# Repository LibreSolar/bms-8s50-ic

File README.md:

# BMS 8S50 IC

 First boards tested, some issues might still be open.

Schematic: [PDF file](https://github.com/LibreSolar/bms-8s50-ic/raw/master/build/bms-8s50-ic_schematic.pdf)

Bill of Materials: [CSV file](build/bms-8s50-ic_bom.csv) or [interactive HTML BOM](https://libre.solar/bms-8s50-ic/build/bms-8s50-ic_ibom.html)

Firmware repository: [LibreSolar/bms-firmware](https://github.com/LibreSolar/bms-firmware)

## Features:

- 3 to 8 Li-ion cells (e.g. LiFePO4)
- Integrated high-side MOSFET switch and current sensor
- Balancing current approx. 150 mA
- STM32L452 ARM Cortex-M4 microcontroller
- Built-in CAN communication interface and UEXT extension connector

## Firmware

The firmware is developed in a separate repository [LibreSolar/bms-firmware](https://github.com/LibreSolar/bms-firmware).

## Housing

The PCB is designed such that a heat sink can be easily attached at the bottom. The following images show a draft idea for the housing. The files of the heat sink and the cover can be found in the `housing` folder as native FreeCAD files.

## Important Notice

The PCBs have not been tested regarding EMC and other regulations. If you reproduce the boards, you use them at your own risk and responsibility.

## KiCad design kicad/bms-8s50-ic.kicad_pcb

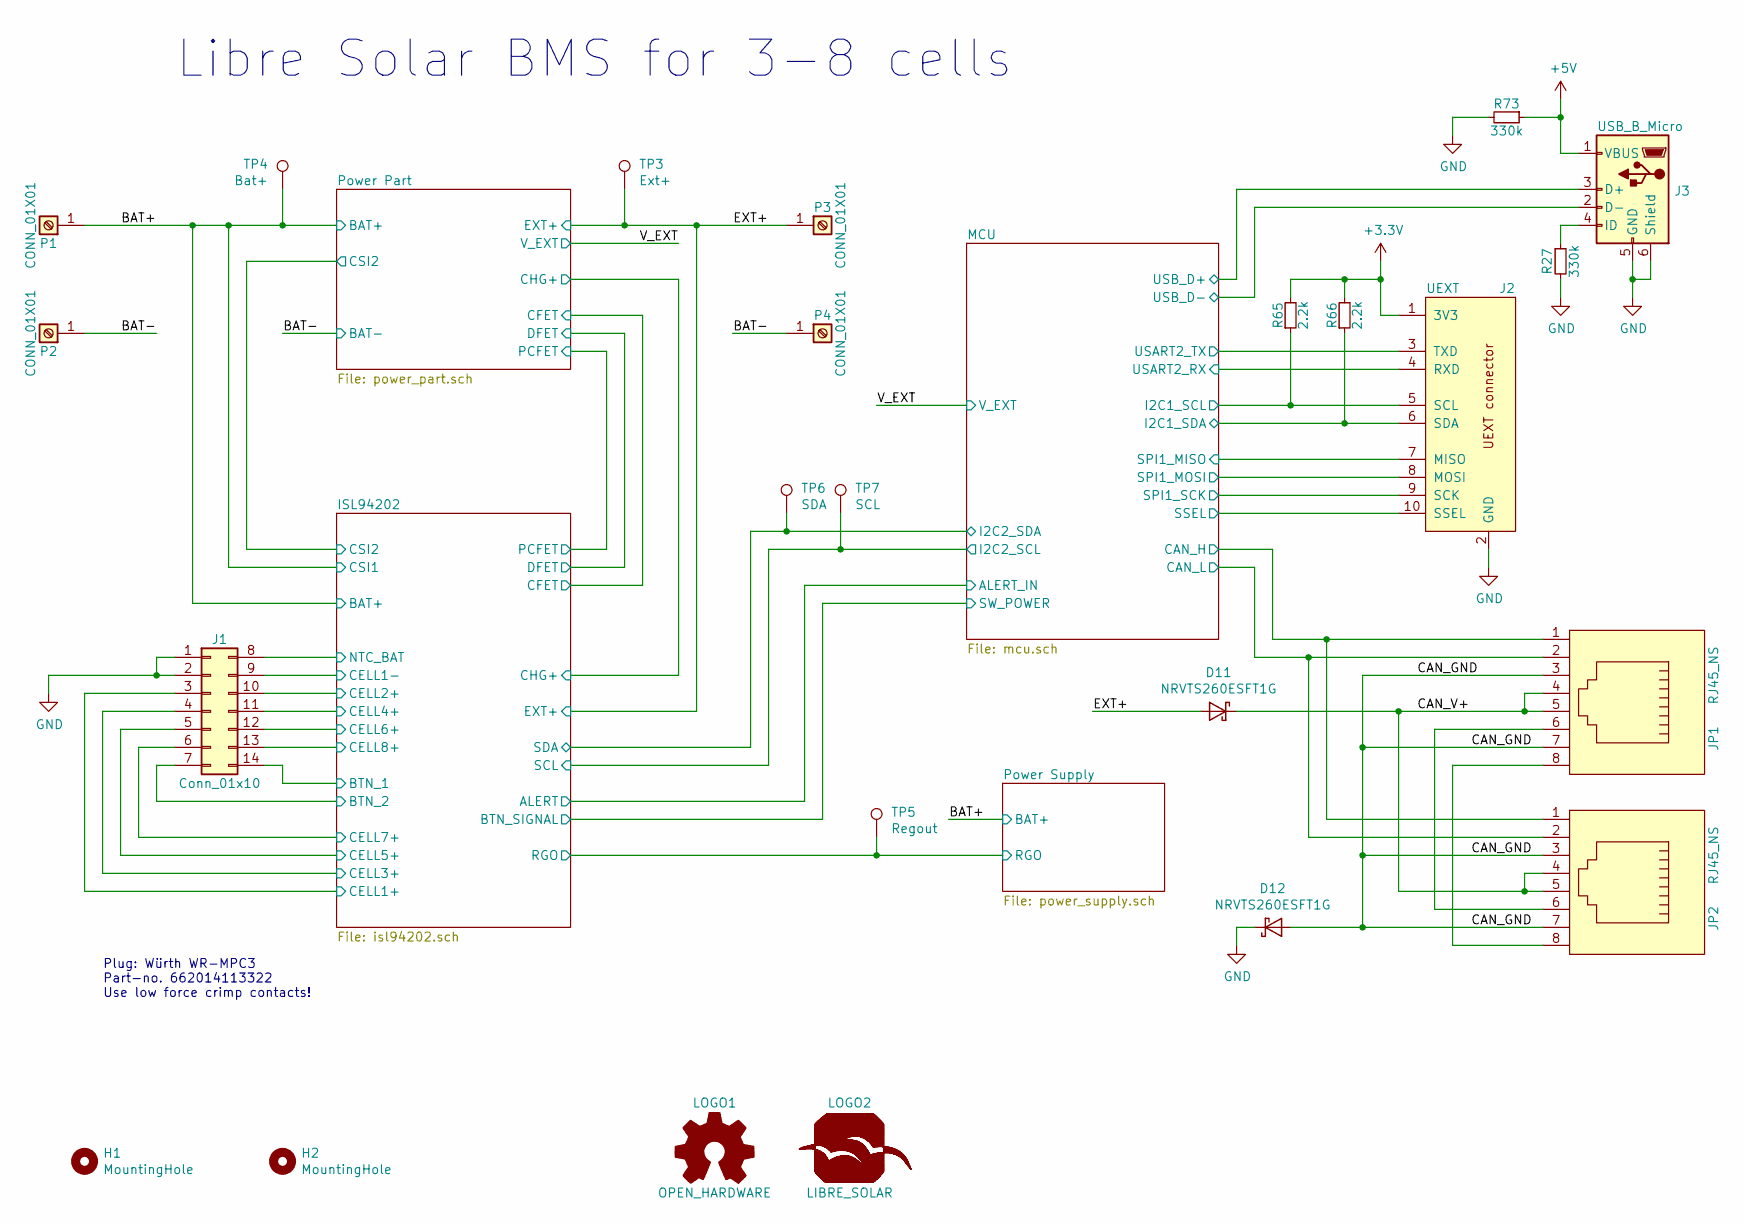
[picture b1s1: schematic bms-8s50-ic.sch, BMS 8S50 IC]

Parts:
D11, D12: NRVTS260ESFT1G; D_SOD-123; PartNumber NRVTS260ESFT1G
H1, H2: MountingHole; MountingHole_3.2mm_M3_Pad
J1: Conn_01x10; Molex_Micro-Fit_3.0_43045-1400_2x07_P3.00mm_Horizontal; PartNumber 66201421022
J2: UEXT; Box_Header_2x05x2.54mm_Straight; PartNumber 61201021621
J3: USB_B_Micro; USB_Micro-B_10103594-0001LF; PartNumber 10103594-0001LF
JP1, JP2: RJ45_NS; RJ45_8P8C; PartNumber 54602-908LF
LOGO1: OPEN_HARDWARE; OSHW-Logo_5.7x6mm_SilkScreen
LOGO2: LIBRE_SOLAR; LIBRESOLAR_LOGO
P1, P2, P4: CONN_01X01; Wuerth_WP-THRBU_74650195; PartNumber 74650195
P3: CONN_01X01; Wuerth_WP-THRBU_74650195
R27, R73: 330k; R_0603_1608; PartNumber RC0603FR-07330KL
R65, R66: 2.2k; R_0603_1608; PartNumber RC0603FR-072K2L
TP3: Ext+; TestPoint_1mm_pad
TP4: Bat+; TestPoint_1mm_pad
TP5: Regout; TestPoint_1mm_pad
TP6: SDA; TestPoint_1mm_pad
TP7: SCL; TestPoint_1mm_pad

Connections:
+3V3: J2.1 (3V3), R65.2, R66.2; also elsewhere on the board
+5V: J3.1 (VBUS), R73.1; also elsewhere on the board
/BAT+: P1.1, TP4.1; also elsewhere on the board
/BAT-: P2.1, P4.1; also elsewhere on the board
/CAN_GND: D12.2 (A), JP1.3, JP1.7, JP2.3, JP2.7
/CAN_V+: D11.1 (K), JP1.4, JP1.5, JP2.4, JP2.5
/EXT+: D11.2 (A), P3.1, TP3.1; also elsewhere on the board
/ISL94202/BTN_1: J1.14; also elsewhere on the board
/ISL94202/BTN_2: J1.7; also elsewhere on the board
/ISL94202/CELL1+: J1.3; also elsewhere on the board
/ISL94202/CELL1-: J1.9; also elsewhere on the board
/ISL94202/CELL2+: J1.10; also elsewhere on the board
/ISL94202/CELL3+: J1.4; also elsewhere on the board
/ISL94202/CELL4+: J1.11; also elsewhere on the board
/ISL94202/CELL5+: J1.5; also elsewhere on the board
/ISL94202/CELL6+: J1.12; also elsewhere on the board
/ISL94202/CELL7+: J1.6; also elsewhere on the board
/ISL94202/CELL8+: J1.13; also elsewhere on the board
/ISL94202/NTC_BAT: J1.8; also elsewhere on the board
/ISL94202/RGO: TP5.1; also elsewhere on the board
/MCU/CAN_H: JP1.1, JP2.1; also elsewhere on the board
/MCU/CAN_L: JP1.2, JP2.2; also elsewhere on the board
/MCU/I2C1_SCL: J2.5 (SCL), R65.1; also elsewhere on the board
/MCU/I2C1_SDA: J2.6 (SDA), R66.1; also elsewhere on the board
/MCU/I2C2_SCL: TP7.1; also elsewhere on the board
/MCU/I2C2_SDA: TP6.1; also elsewhere on the board
/MCU/SPI1_MISO: J2.7 (MISO); also elsewhere on the board
/MCU/SPI1_MOSI: J2.8 (MOSI); also elsewhere on the board
/MCU/SPI1_SCK: J2.9 (SCK); also elsewhere on the board
/MCU/SSEL: J2.10 (SSEL); also elsewhere on the board
/MCU/USART2_RX: J2.4 (RXD); also elsewhere on the board
/MCU/USART2_TX: J2.3 (TXD); also elsewhere on the board
/MCU/USB_D+: J3.3 (D+); also elsewhere on the board
/MCU/USB_D-: J3.2 (D-); also elsewhere on the board
GND: D12.1 (K), J1.1, J1.2, J2.2 (GND), J3.5 (GND), J3.6 (Shield), R27.2, R73.2; also elsewhere on the board
unnamed: J3.4 (ID), R27.1
unnamed: JP1.6, JP2.6
unnamed: JP1.8, JP2.8

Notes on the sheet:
Plug: Würth WR-MPC3 Part-no. 662014113322 Use low force crimp contacts!
Libre Solar BMS for 3-8 cells

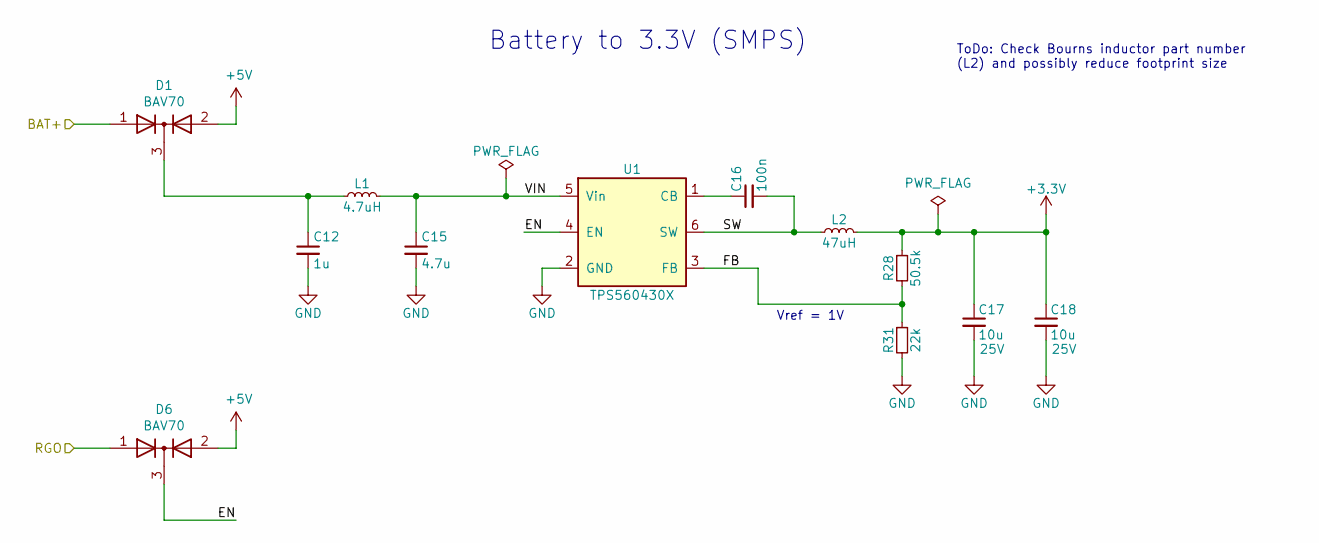
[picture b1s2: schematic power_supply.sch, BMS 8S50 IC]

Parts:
C12: 1u; C_0603_1608; PartNumber GRT188R61H105KE13D
C15: 4.7u; C_1210_3225; PartNumber GRM31CR71H475MA12L
C16: 100n; C_0603_1608; PartNumber CC0603KRX7R9BB104
C17, C18: 10u; C_0805_2012; PartNumber GRM21BR61E106KA73L
D1, D6: BAV70; SOT-23; PartNumber BAV70LT1G
L1: 4.7uH; L_0805_2012Metric; PartNumber LQM21PN4R7NGRD
L2: 47uH; Bourns_SRN6045TA; PartNumber NR6045T470M
R28: 50.5k; R_0603_1608; PartNumber RC0603FR-0750K5L
R31: 22k; R_0603_1608; PartNumber RC0603FR-0722KL
U1: TPS560430X; SOT-23-6; PartNumber TPS560430XDBVR

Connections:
+3V3: C17.1, C18.1, L2.2, R28.1; also elsewhere on the board
+5V: D1.2 (A), D6.2 (A); also elsewhere on the board
/BAT+: D1.1 (A); also elsewhere on the board
/ISL94202/RGO: D6.1 (A); also elsewhere on the board
/Power Supply/EN: D6.3 (K), U1.4 (EN)
/Power Supply/FB: R28.2, R31.1, U1.3 (FB)
/Power Supply/SW: C16.2, L2.1, U1.6 (SW)
/Power Supply/VIN: C15.1, L1.2, U1.5 (Vin)
GND: C12.2, C15.2, C17.2, C18.2, R31.2, U1.2 (GND); also elsewhere on the board
unnamed: C12.1, D1.3 (K), L1.1
unnamed: C16.1, U1.1 (CB)

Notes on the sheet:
Battery to 3.3V (SMPS)
ToDo: Check Bourns inductor part number (L2) and possibly reduce footprint size
Vref = 1V

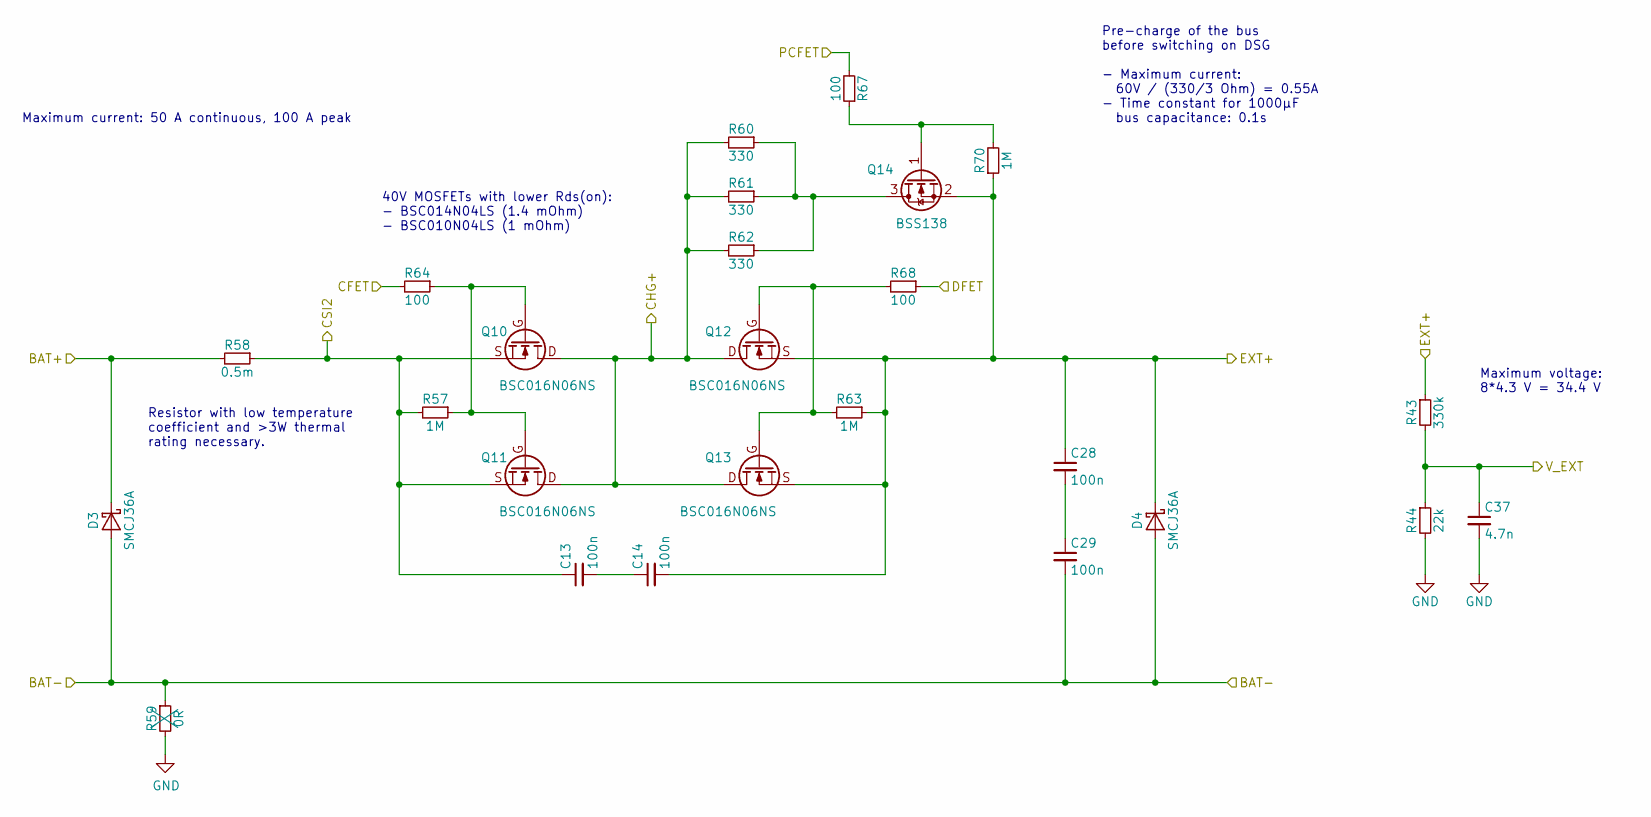
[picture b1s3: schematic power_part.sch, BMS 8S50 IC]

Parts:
C13, C14, C28, C29: 100n; C_0603_1608; PartNumber CC0603KRX7R9BB104
C37: 4.7n; C_0603_1608; PartNumber CC0603KRX7R9BB472
D3, D4: SMCJ36A; D_SMC; PartNumber SMCJ24A
Q10, Q11, Q12, Q13: BSC016N06NS; 5X6_MOSFET; PartNumber BSC016N06NS
Q14: BSS138; SOT-23; PartNumber BSS138
R43: 330k; R_0603_1608; PartNumber RC0603FR-07330KL
R44: 22k; R_0603_1608; PartNumber RC0603FR-0722KL
R57, R63, R70: 1M; R_0603_1608; PartNumber RC0603FR-071ML
R58: 0.5m; R_Shunt_2512; PartNumber WSLF2512L5000FEA
R59: 0R; R_0603_1608; PartNumber RC0603FR-070RL
R60, R61, R62: 330; R_2010_5025; PartNumber RC2010JK-07330RL
R64, R67, R68: 100; R_0603_1608; PartNumber RC0603FR-07100RL

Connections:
/BAT+: D3.1 (K), R58.2; also elsewhere on the board
/BAT-: C29.2, D3.2 (A), D4.2 (A), R59.1; also elsewhere on the board
/EXT+: C14.2, C28.1, D4.1 (K), Q12.S, Q13.S, Q14.2 (S), R43.1, R63.1, R70.1; also elsewhere on the board
/ISL94202/CFET: R64.2; also elsewhere on the board
/ISL94202/CHG+: Q10.D, Q11.D, Q12.D, Q13.D, R60.2, R61.2, R62.2; also elsewhere on the board
/ISL94202/CSI2: C13.1, Q10.S, Q11.S, R57.2, R58.1; also elsewhere on the board
/ISL94202/DFET: R68.1; also elsewhere on the board
/ISL94202/PCFET: R67.2; also elsewhere on the board
/V_EXT: C37.1, R43.2, R44.1; also elsewhere on the board
GND: C37.2, R44.2, R59.2; also elsewhere on the board
unnamed: C13.2, C14.1
unnamed: C28.2, C29.1
unnamed: Q10.G, Q11.G, R57.1, R64.1
unnamed: Q12.G, Q13.G, R63.2, R68.2
unnamed: Q14.1 (G), R67.1, R70.2
unnamed: Q14.3 (D), R60.1, R61.1, R62.1

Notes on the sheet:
Pre-charge of the bus before switching on DSG - Maximum current: 60V / (330/3 Ohm) = 0.55A - Time constant for 1000µF bus capacitance: 0.1s
Resistor with low temperature coefficient and >3W thermal rating necessary.
Maximum current: 50 A continuous, 100 A peak
40V MOSFETs with lower Rds(on): - BSC014N04LS (1.4 mOhm) - BSC010N04LS (1 mOhm)
Maximum voltage: 8*4.3 V = 34.4 V

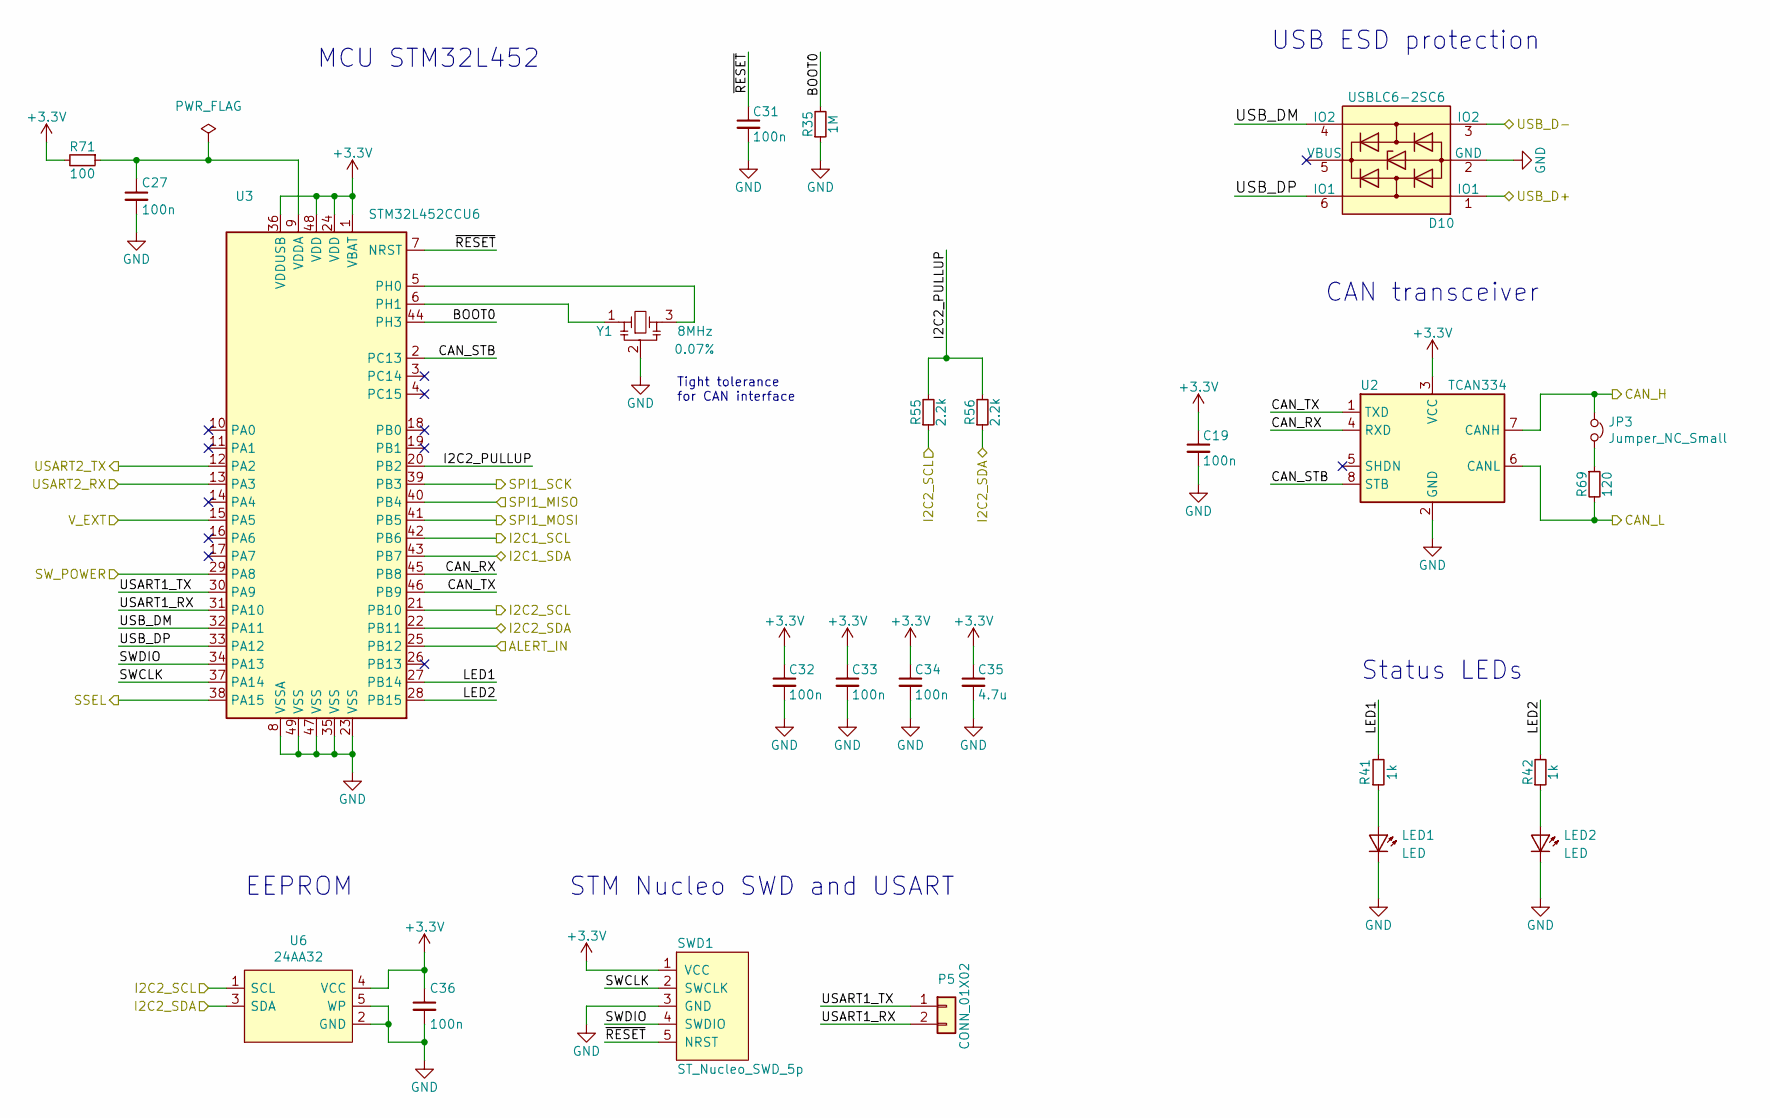
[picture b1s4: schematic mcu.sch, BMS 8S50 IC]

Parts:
C19, C27, C31, C32, C33, C34, C36: 100n; C_0603_1608; PartNumber CC0603KRX7R9BB104
C35: 4.7u; C_0603_1608; PartNumber GRM188R61A475KE15D
D10: USBLC6-2SC6; SOT-23-6; PartNumber USBLC6-2SC6
JP3: Jumper_NC_Small; PinHeader_1x02_P2.54mm_Vertical
LED1, LED2: LED; LED_0603_D3.0mm
P5: CONN_01X02; PinHeader_1x02_P2.54mm_Vertical
R35: 1M; R_0603_1608; PartNumber RC0603FR-071ML
R41, R42: 1k; R_0603_1608; PartNumber RC0603FR-071KL
R55, R56: 2.2k; R_0603_1608; PartNumber RC0603FR-072K2L
R69: 120; R_1206_3216; PartNumber RC1206FR-07120RL
R71: 100; R_0603_1608; PartNumber RC0603FR-07100RL
SWD1: ST_Nucleo_SWD_5p; PinHeader_1x05_P2.54mm_Vertical
U2: TCAN334; SOIC-8_3.9x4.9mm_Pitch1.27mm; PartNumber TCAN334DR
U3: STM32L452CCU6; QFN-48-1EP_7x7mm_P0.5mm_EP5.6x5.6mm; PartNumber STM32L452CCU6
U6: 24AA32; SOT-23-5; PartNumber 24AA32AFT-I/OT
Y1: 8MHz; Resonator_Murata_CSTNE; PartNumber CSTNE8M00GH5C000R0

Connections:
+3V3: C19.1, C32.1, C33.1, C34.1, C35.1, C36.1, R71.2, SWD1.1 (VCC), U2.3 (VCC), U3.1 (VBAT), U3.24 (VDD), U3.36 (VDDUSB), U3.48 (VDD), U6.4 (VCC); also elsewhere on the board
/ISL94202/ALERT: U3.25 (PB12); also elsewhere on the board
/ISL94202/BTN_SIGNAL: U3.29 (PA8); also elsewhere on the board
/MCU/BOOT0: R35.2, U3.44 (PH3)
/MCU/CAN_H: JP3.1, U2.7 (CANH); also elsewhere on the board
/MCU/CAN_L: R69.2, U2.6 (CANL); also elsewhere on the board
/MCU/CAN_RX: U2.4 (RXD), U3.45 (PB8)
/MCU/CAN_STB: U2.8 (STB), U3.2 (PC13)
/MCU/CAN_TX: U2.1 (TXD), U3.46 (PB9)
/MCU/I2C1_SCL: U3.42 (PB6); also elsewhere on the board
/MCU/I2C1_SDA: U3.43 (PB7); also elsewhere on the board
/MCU/I2C2_PULLUP: R55.2, R56.2, U3.20 (PB2)
/MCU/I2C2_SCL: R55.1, U3.21 (PB10), U6.1 (SCL); also elsewhere on the board
/MCU/I2C2_SDA: R56.1, U3.22 (PB11), U6.3 (SDA); also elsewhere on the board
/MCU/LED1: R41.2, U3.27 (PB14)
/MCU/LED2: R42.2, U3.28 (PB15)
/MCU/SPI1_MISO: U3.40 (PB4); also elsewhere on the board
/MCU/SPI1_MOSI: U3.41 (PB5); also elsewhere on the board
/MCU/SPI1_SCK: U3.39 (PB3); also elsewhere on the board
/MCU/SSEL: U3.38 (PA15); also elsewhere on the board
/MCU/SWCLK: SWD1.2 (SWCLK), U3.37 (PA14)
/MCU/SWDIO: SWD1.4 (SWDIO), U3.34 (PA13)
/MCU/USART1_RX: P5.2, U3.31 (PA10)
/MCU/USART1_TX: P5.1, U3.30 (PA9)
/MCU/USART2_RX: U3.13 (PA3); also elsewhere on the board
/MCU/USART2_TX: U3.12 (PA2); also elsewhere on the board
/MCU/USB_D+: D10.1 (IO1); also elsewhere on the board
/MCU/USB_D-: D10.3 (IO2); also elsewhere on the board
/MCU/USB_DM: D10.4 (IO2), U3.32 (PA11)
/MCU/USB_DP: D10.6 (IO1), U3.33 (PA12)
/MCU/~RESET: C31.1, SWD1.5 (NRST), U3.7 (NRST)
/V_EXT: U3.15 (PA5); also elsewhere on the board
GND: C19.2, C27.2, C31.2, C32.2, C33.2, C34.2, C35.2, C36.2, D10.2 (GND), LED1.1 (K), LED2.1 (K), R35.1, SWD1.3 (GND), U2.2 (GND), U3.8 (VSSA), U3.23 (VSS), U3.35 (VSS), U3.47 (VSS), U3.49 (VSS), U6.2 (GND), U6.5 (WP), Y1.2; also elsewhere on the board
unnamed: C27.1, R71.1, U3.9 (VDDA)
unnamed: JP3.2, R69.1
unnamed: LED1.2 (A), R41.1
unnamed: LED2.2 (A), R42.1
unnamed: U3.5 (PH0), Y1.3
unnamed: U3.6 (PH1), Y1.1

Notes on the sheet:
Status LEDs
MCU STM32L452
STM Nucleo SWD and USART
EEPROM
USB ESD protection
CAN transceiver
Tight tolerance for CAN interface

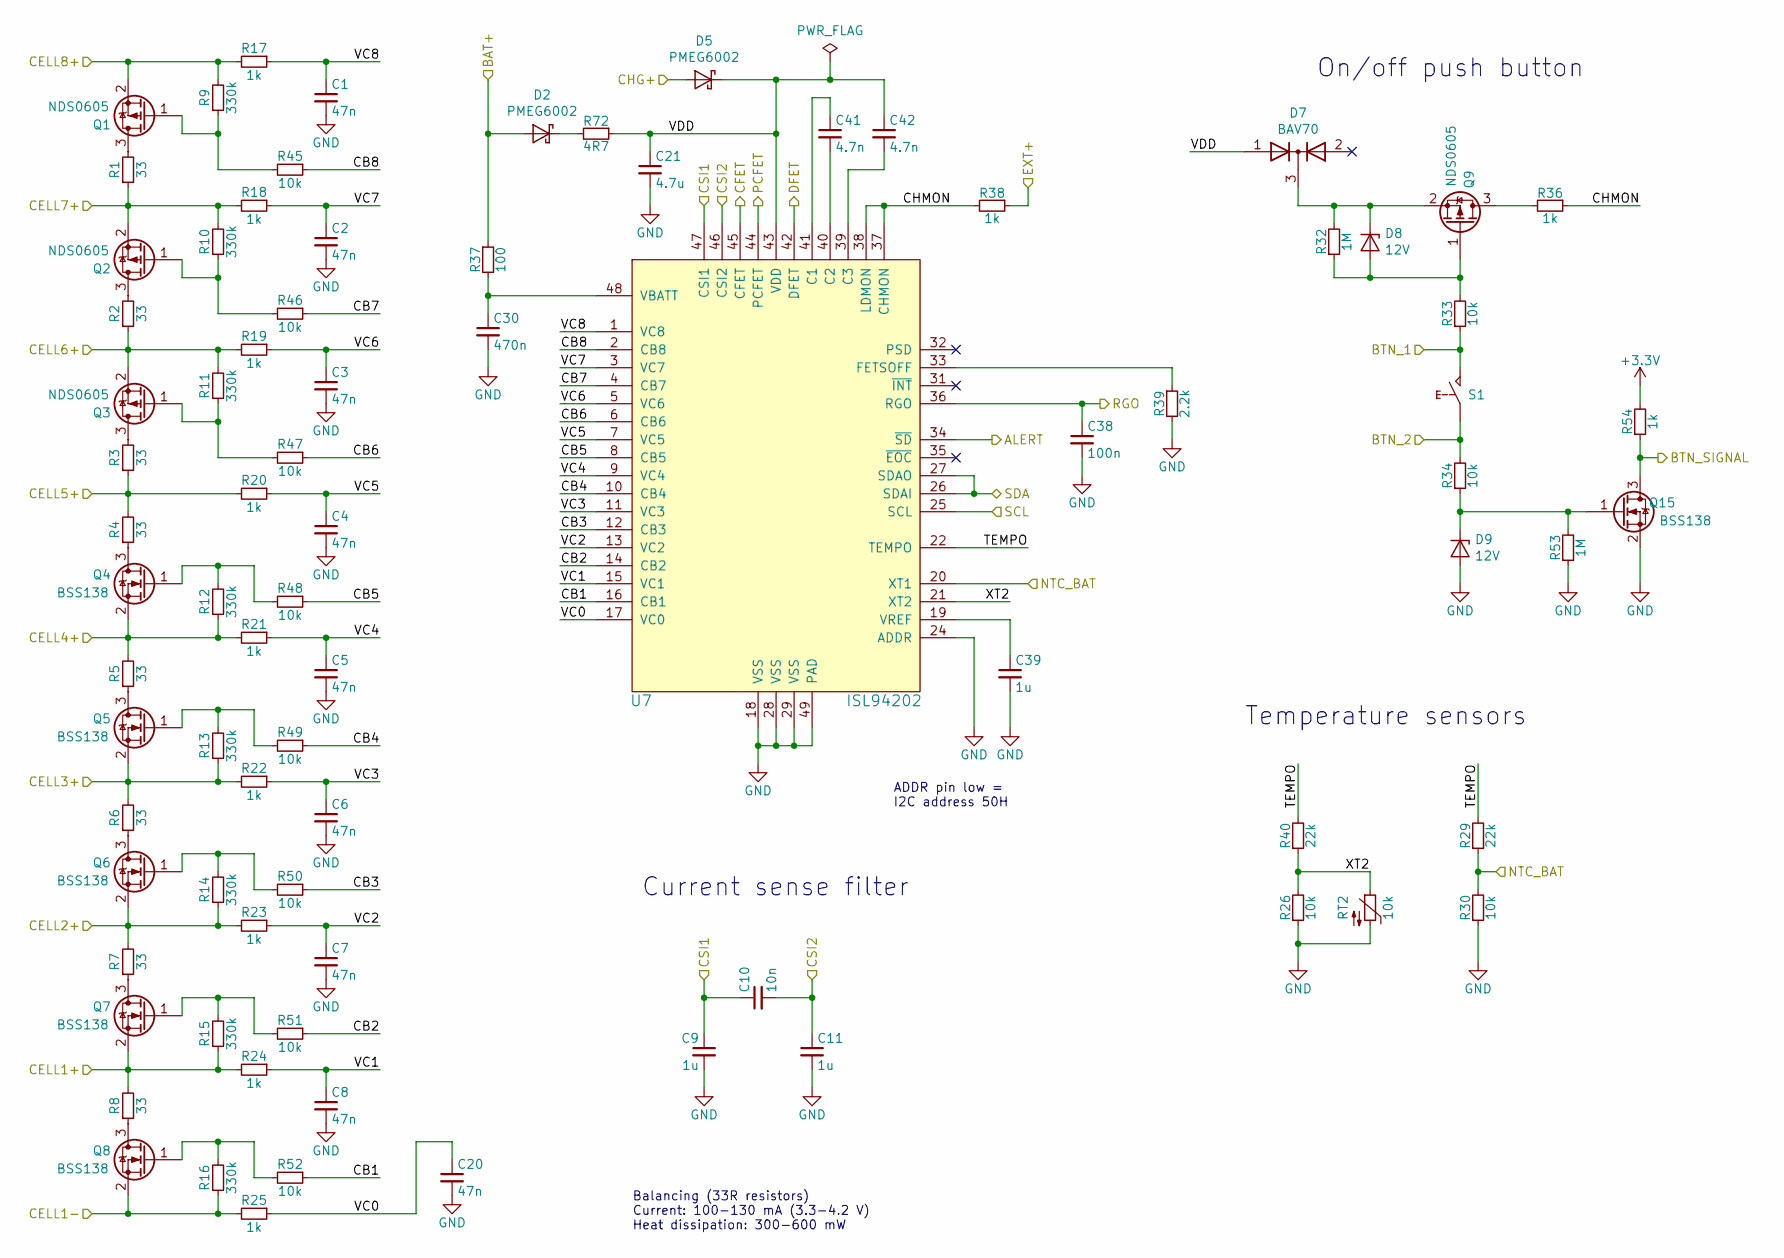
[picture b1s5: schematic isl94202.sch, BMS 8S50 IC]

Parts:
C1, C2, C3, C4, C5, C6, C7, C8, C20: 47n; C_0603_1608; PartNumber CC0603KRX7R9BB473
C9, C11: 1u; C_0603_1608; PartNumber GRT188R61H105KE13D
C10: 10n; C_0603_1608
C21: 4.7u; C_1206_3216; PartNumber GRM31CR71H475MA12L
C30: 470n; C_0603_1608
C38: 100n; C_0603_1608; PartNumber CC0603KRX7R9BB104
C39: 1u; C_0603_1608
C41, C42: 4.7n; C_0603_1608; PartNumber CC0603KRX7R9BB472
D2, D5: PMEG6002; D_SOD-523; PartNumber PMEG6002EBF
D7: BAV70; SOT-23; PartNumber BAV70LT1G
D8, D9: 12V; D_SOT-23_ANK; PartNumber SZBZX84C12LT3G
Q1, Q2, Q3, Q9: NDS0605; SOT-23; PartNumber NDS0605
Q4, Q5, Q6, Q7, Q8, Q15: BSS138; SOT-23; PartNumber BSS138
R1, R2, R3, R4, R5, R6, R7, R8: 33; R_2010_5025; PartNumber RC2010JK-0733RL
R9, R10, R11, R12, R13, R14, R15, R16: 330k; R_0603_1608; PartNumber RC0603FR-07330KL
R17, R18, R19, R20, R21, R22, R23, R24, R25, R36, R38, R54: 1k; R_0603_1608; PartNumber RC0603FR-071KL
R26, R30, R33, R34, R45, R46, R47, R48, R49, R50, R51, R52: 10k; R_0603_1608; PartNumber RC0603FR-0710KL
R29, R40: 22k; R_0603_1608; PartNumber RC0603FR-0722KL
R32: 1M; R_0603_1608
R37: 100; R_0603_1608; PartNumber RC0603FR-07100RL
R39: 2.2k; R_0603_1608; PartNumber RC0603FR-072K2L
R53: 1M; R_0603_1608; PartNumber RC0603FR-071ML
R72: 4R7; R_0603_1608; PartNumber RC0603FR-071KL
RT2: 10k; R_0603_1608; PartNumber NTCG163JF103FT1S
S1: SW_PUSH; SW_SPST_6mm
U7: ISL94202; QFN-48-1EP_6x6mm_P0.4mm_EP4.3x4.3mm; PartNumber ISL94202IRTZ-T7A

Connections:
+3V3: R54.2; also elsewhere on the board
/BAT+: C9.1, C10.1, D2.2 (A), R37.1, U7.47 (CSI1); also elsewhere on the board
/EXT+: R38.1; also elsewhere on the board
/ISL94202/ALERT: U7.34 (~SD); also elsewhere on the board
/ISL94202/BTN_1: R33.1, S1.2; also elsewhere on the board
/ISL94202/BTN_2: R34.2, S1.1; also elsewhere on the board
/ISL94202/BTN_SIGNAL: Q15.3 (D), R54.1; also elsewhere on the board
/ISL94202/CB1: R52.1, U7.16 (CB1)
/ISL94202/CB2: R51.1, U7.14 (CB2)
/ISL94202/CB3: R50.1, U7.12 (CB3)
/ISL94202/CB4: R49.1, U7.10 (CB4)
/ISL94202/CB5: R48.1, U7.8 (CB5)
/ISL94202/CB6: R47.1, U7.6 (CB6)
/ISL94202/CB7: R46.1, U7.4 (CB7)
/ISL94202/CB8: R45.1, U7.2 (CB8)
/ISL94202/CELL1+: Q7.2 (S), R8.2, R15.1, R24.2; also elsewhere on the board
/ISL94202/CELL1-: Q8.2 (S), R16.1, R25.2; also elsewhere on the board
/ISL94202/CELL2+: Q6.2 (S), R7.2, R14.1, R23.2; also elsewhere on the board
/ISL94202/CELL3+: Q5.2 (S), R6.2, R13.1, R22.2; also elsewhere on the board
/ISL94202/CELL4+: Q4.2 (S), R5.2, R12.1, R21.2; also elsewhere on the board
/ISL94202/CELL5+: R3.1, R4.2, R20.2; also elsewhere on the board
/ISL94202/CELL6+: Q3.2 (S), R2.1, R11.2, R19.2; also elsewhere on the board
/ISL94202/CELL7+: Q2.2 (S), R1.1, R10.2, R18.2; also elsewhere on the board
/ISL94202/CELL8+: Q1.2 (S), R9.2, R17.2; also elsewhere on the board
/ISL94202/CFET: U7.45 (CFET); also elsewhere on the board
/ISL94202/CHG+: D5.2 (A); also elsewhere on the board
/ISL94202/CHMON: R36.1, R38.2, U7.37 (CHMON), U7.38 (LDMON)
/ISL94202/CSI2: C10.2, C11.1, U7.46 (CSI2); also elsewhere on the board
/ISL94202/DFET: U7.42 (DFET); also elsewhere on the board
/ISL94202/NTC_BAT: R29.1, R30.2, U7.20 (XT1); also elsewhere on the board
/ISL94202/PCFET: U7.44 (PCFET); also elsewhere on the board
/ISL94202/RGO: C38.1, U7.36 (RGO); also elsewhere on the board
/ISL94202/TEMPO: R29.2, R40.2, U7.22 (TEMPO)
/ISL94202/VC0: C20.1, R25.1, U7.17 (VC0)
/ISL94202/VC1: C8.1, R24.1, U7.15 (VC1)
/ISL94202/VC2: C7.1, R23.1, U7.13 (VC2)
/ISL94202/VC3: C6.1, R22.1, U7.11 (VC3)
/ISL94202/VC4: C5.1, R21.1, U7.9 (VC4)
/ISL94202/VC5: C4.1, R20.1, U7.7 (VC5)
/ISL94202/VC6: C3.1, R19.1, U7.5 (VC6)
/ISL94202/VC7: C2.1, R18.1, U7.3 (VC7)
/ISL94202/VC8: C1.1, R17.1, U7.1 (VC8)
/ISL94202/VDD: C21.1, C42.1, D5.1 (K), D7.1 (A), R72.1, U7.43 (VDD)
/ISL94202/XT2: R26.2, R40.1, RT2.1, U7.21 (XT2)
/MCU/I2C2_SCL: U7.25 (SCL); also elsewhere on the board
/MCU/I2C2_SDA: U7.26 (SDAI), U7.27 (SDAO); also elsewhere on the board
GND: C1.2, C2.2, C3.2, C4.2, C5.2, C6.2, C7.2, C8.2, C9.2, C11.2, C20.2, C21.2, C30.2, C38.2, C39.2, D9.2 (A), Q15.2 (S), R26.1, R30.1, R39.2, R53.1, RT2.2, U7.18 (VSS), U7.24 (ADDR), U7.28 (VSS), U7.29 (VSS), U7.49 (PAD); also elsewhere on the board
unnamed: C30.1, R37.2, U7.48 (VBATT)
unnamed: C39.1, U7.19 (VREF)
unnamed: C41.1, U7.41 (C1)
unnamed: C41.2, U7.40 (C2)
unnamed: C42.2, U7.39 (C3)
unnamed: D2.1 (K), R72.2
unnamed: D7.3 (K), D8.1 (K), Q9.2 (S), R32.2
unnamed: D8.2 (A), Q9.1 (G), R32.1, R33.2
unnamed: D9.1 (K), Q15.1 (G), R34.1, R53.2
unnamed: Q1.1 (G), R9.1, R45.2
unnamed: Q1.3 (D), R1.2
unnamed: Q2.1 (G), R10.1, R46.2
unnamed: Q2.3 (D), R2.2
unnamed: Q3.1 (G), R11.1, R47.2
unnamed: Q3.3 (D), R3.2
unnamed: Q4.1 (G), R12.2, R48.2
unnamed: Q4.3 (D), R4.1
unnamed: Q5.1 (G), R13.2, R49.2
unnamed: Q5.3 (D), R5.1
unnamed: Q6.1 (G), R14.2, R50.2
unnamed: Q6.3 (D), R6.1
unnamed: Q7.1 (G), R15.2, R51.2
unnamed: Q7.3 (D), R7.1
unnamed: Q8.1 (G), R16.2, R52.2
unnamed: Q8.3 (D), R8.1
unnamed: Q9.3 (D), R36.2
unnamed: R39.1, U7.33 (FETSOFF)

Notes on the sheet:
Balancing (33R resistors) Current: 100-130 mA (3.3-4.2 V) Heat dissipation: 300-600 mW
Current sense filter
Temperature sensors
On/off push button
ADDR pin low = I2C address 50H

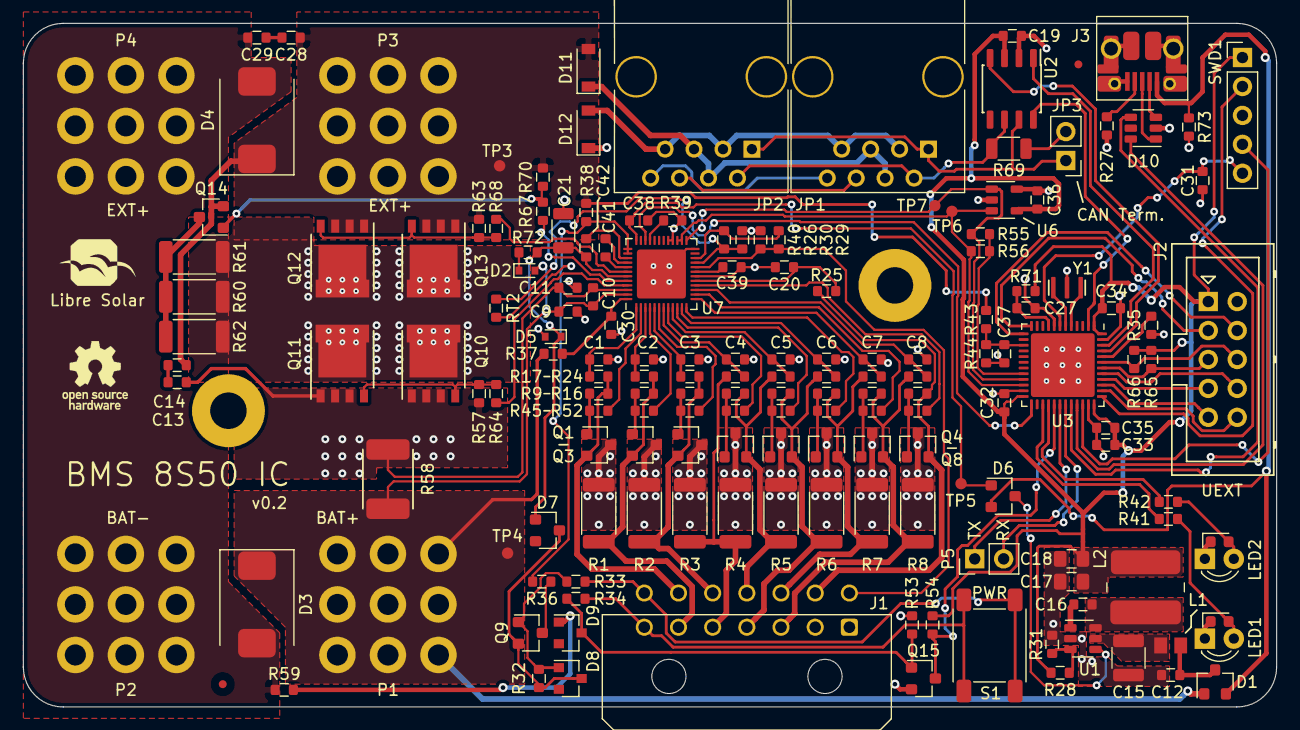
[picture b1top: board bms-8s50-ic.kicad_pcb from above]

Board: 2 copper layers, 110.0 x 60.0 mm, 169 parts (0 on the bottom side), 126 nets.

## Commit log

2019-08-12 Draft housing design added
2020-05-08 Fix issues found during testing (v0.1.1)
    - Add BAT+/- and EXT+/- markings to terminals (#2)
    - Change C30 to 470nF (#5)
    - Add C20 (47nF) at VC0 pin (#5)
    - Add C21 and R72 for proper low-pass filter of VDD (#5)
    - Change C39 at VREF to 1uF (#5)
    - Add R70: Pull-down for PCHG FET (#5)
2020-06-08 Add KiCad symbol cache and remove rescue lib
2021-02-14 Update to v0.2
    - Switch to STM32L452 MCU (STM32F072 has too little RAM for CAN ISO-TP etc.)
    - Add CAN termination jumper
    - Add CAN bus power supply diodes
    - Update CAN connector to match LS.bus spec
    - Add interactive BOM and CSV BOM to build directory
    - Add additional thermal vias with 0.2mm diameter under MOSFETs

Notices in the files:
kicad/bms-8s50-ic.kicad_pcb:
License: CC-BY-SA
kicad/bms-8s50-ic.sch:
License: Creative Commons Attribution-ShareAlike 4.0 International
